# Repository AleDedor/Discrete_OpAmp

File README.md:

# Discrete_OpAmp
A Single Ended Operational Amplifier mainly made with bipolar technology and a NMOS differential pair, two amplification stages and a Class AB output stage. Entirely designed with discrete components, soldered onto a self-made, 2 layers PCB.

## Final results, in lab tests:

- +-5V dual power supply, 10 mA current absorption, buffer configuration.
- GBWP > 3Mhz.
- HD2 = 40dB (second harmonic distortion).
- Slew Rate = 1.5V/us.
- Offset = 50mV.

## Soldered PCB image:

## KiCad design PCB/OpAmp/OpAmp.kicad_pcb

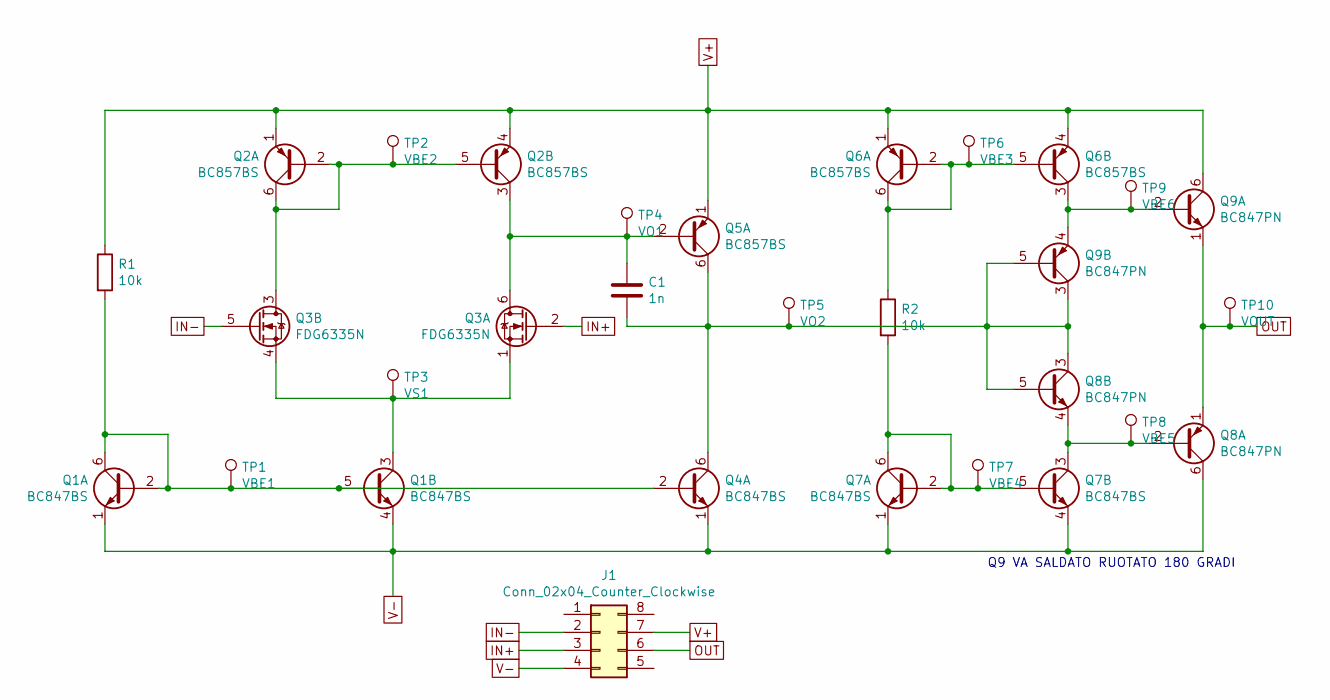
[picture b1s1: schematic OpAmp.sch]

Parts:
C1: 1n; C_0805_2012Metric_Pad1.18x1.45mm_HandSolder
J1: Conn_02x04_Counter_Clockwise; DIP-8_W7.62mm_Socket
Q1, Q4, Q7: BC847BS; SOT-363_SC-70-6
Q2, Q5, Q6: BC857BS; SOT-363_SC-70-6
Q3: FDG6335N; SOT-363_SC-70-6
Q8, Q9: BC847PN; SOT-363_SC-70-6
R1, R2: 10k; R_0805_2012Metric_Pad1.20x1.40mm_HandSolder
TP1: VBE1; TestPoint_THTPad_D1.5mm_Drill0.7mm
TP2: VBE2; TestPoint_THTPad_D1.5mm_Drill0.7mm
TP3: VS1; TestPoint_THTPad_D1.5mm_Drill0.7mm
TP4: VO1; TestPoint_THTPad_D1.5mm_Drill0.7mm
TP5: VO2; TestPoint_THTPad_D1.5mm_Drill0.7mm
TP6: VBE3; TestPoint_THTPad_D1.5mm_Drill0.7mm
TP7: VBE4; TestPoint_THTPad_D1.5mm_Drill0.7mm
TP8: VBE5; TestPoint_THTPad_D1.5mm_Drill0.7mm
TP9: VBE6; TestPoint_THTPad_D1.5mm_Drill0.7mm
TP10: VOUT; TestPoint_THTPad_D1.5mm_Drill0.7mm

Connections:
IN+: J1.3, Q3.2 (G)
IN-: J1.2, Q3.5 (G)
unnamed: C1.1, Q2.3 (C2), Q3.6 (D), Q5.2 (B1), TP4.1
unnamed: C1.2, Q4.6 (C1), Q5.6 (C1), Q8.3 (C2), Q8.5 (B2), Q9.3 (C2), Q9.5 (B2), TP5.1
unnamed: Q1.2 (B1), Q1.5 (B2), Q1.6 (C1), Q4.2 (B1), R1.2, TP1.1
unnamed: Q1.3 (C2), Q3.1 (S), Q3.4 (S), TP3.1
unnamed: Q2.2 (B1), Q2.5 (B2), Q2.6 (C1), Q3.3 (D), TP2.1
unnamed: Q6.2 (B1), Q6.5 (B2), Q6.6 (C1), R2.1, TP6.1
unnamed: Q6.3 (C2), Q9.2 (B1), Q9.4 (E2), TP9.1
unnamed: Q7.2 (B1), Q7.5 (B2), Q7.6 (C1), R2.2, TP7.1
unnamed: Q7.3 (C2), Q8.2 (B1), Q8.4 (E2), TP8.1
OUT: J1.6, Q8.1 (E1), Q9.1 (E1), TP10.1
V+: J1.7, Q2.1 (E1), Q2.4 (E2), Q5.1 (E1), Q6.1 (E1), Q6.4 (E2), Q9.6 (C1), R1.1
V-: J1.4, Q1.1 (E1), Q1.4 (E2), Q4.1 (E1), Q7.1 (E1), Q7.4 (E2), Q8.6 (C1)

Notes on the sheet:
Q9 VA SALDATO RUOTATO 180 GRADI

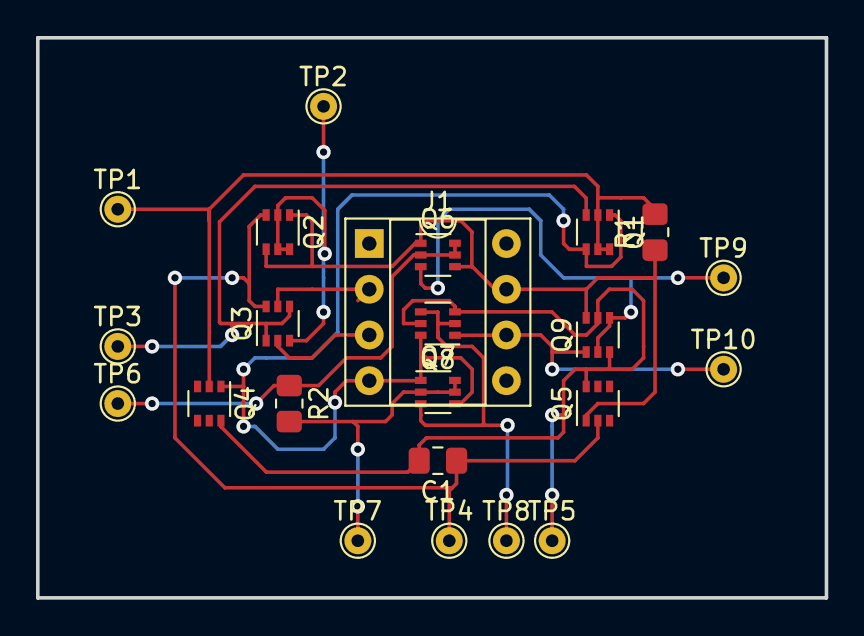
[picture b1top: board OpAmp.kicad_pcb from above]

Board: 2 copper layers, 43.8 x 31.1 mm, 23 parts (0 on the bottom side), 14 nets.

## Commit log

2024-02-24 Added main files
2024-02-24 Update README.md, results
2024-02-24 Image
2024-02-24 Update README.md, image
